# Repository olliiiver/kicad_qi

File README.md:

# Qi module designed in KiCad based on TI bq51013B

This is a "works for me" project. It has not been optimised (foreign object detection, max. output, etc) or tested for (unwanted) electromagnetic radiation.

## Photos

## BOM

- BQ51013BRHLR: http://www.ti.com/lit/ds/symlink/bq51013b.pdf
- 10 µH 0.15 Ω 3 A Coil (Würth  760308102210): https://www.we-online.de/katalog/datasheet/760308102210.pdf
https://www.conrad.de/de/p/wuerth-elektronik-we-wpcc-760308102210-empfaengerspule-qi-kompatibel-wireless-10-h-0-15-3-a-1-1364999.html
- All resistors and caps are 0805. Caps from coil to IC need to be min. 50V

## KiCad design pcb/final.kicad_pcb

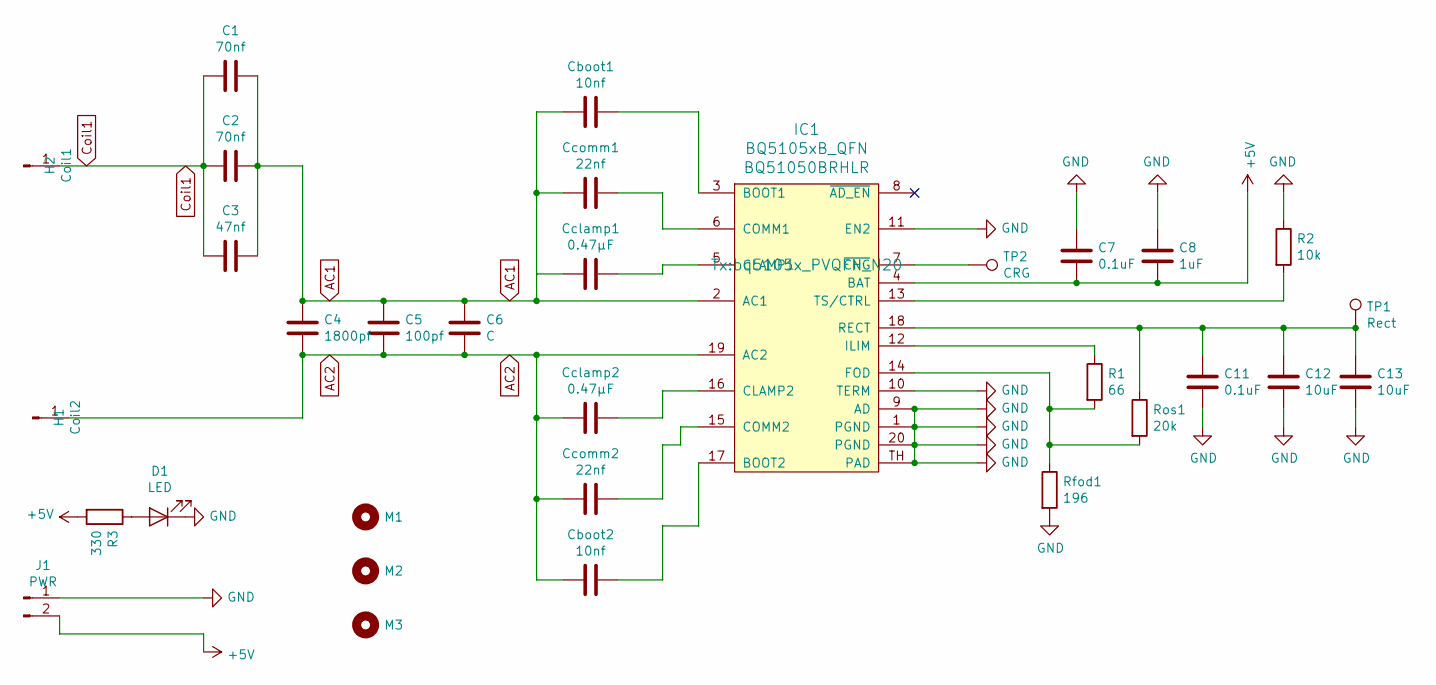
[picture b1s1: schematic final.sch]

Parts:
C1, C2: 70nf; C_0805_2012Metric_Pad1.15x1.40mm_HandSolder
C3: 47nf; C_0805_2012Metric_Pad1.15x1.40mm_HandSolder
C4: 1800pf; C_0805_2012Metric_Pad1.15x1.40mm_HandSolder
C5: 100pf; C_0805_2012Metric_Pad1.15x1.40mm_HandSolder
C6: C; C_0805_2012Metric_Pad1.15x1.40mm_HandSolder
C7, C11: 0.1uF; C_0805_2012Metric_Pad1.15x1.40mm_HandSolder
C8: 1uF; C_0805_2012Metric_Pad1.15x1.40mm_HandSolder
C12, C13: 10uF; C_0805_2012Metric_Pad1.15x1.40mm_HandSolder
Cboot1, Cboot2: 10nf; C_0805_2012Metric_Pad1.15x1.40mm_HandSolder
Cclamp1, Cclamp2: 0.47μF; C_0805_2012Metric_Pad1.15x1.40mm_HandSolder
Ccomm1, Ccomm2: 22nf; C_0805_2012Metric_Pad1.15x1.40mm_HandSolder
Coil1: H2; TestPoint_Pad_3.0x3.0mm
Coil2: H1; TestPoint_Pad_3.0x3.0mm
D1: LED; LED_0805_2012Metric_Pad1.15x1.40mm_HandSolder
IC1: BQ5105xB_QFN; bq5105x_PVQFN_N20; MPN BQ51050BRHLR
J1: PWR; PinHeader_1x02_P2.54mm_Vertical
M1, M2, M3: MountingHole; MountingHole_1152
R1: 66; R_0805_2012Metric_Pad1.15x1.40mm_HandSolder
R2: 10k; R_0805_2012Metric_Pad1.15x1.40mm_HandSolder
R3: 330; R_0805_2012Metric_Pad1.15x1.40mm_HandSolder
Rfod1: 196; R_0805_2012Metric_Pad1.15x1.40mm_HandSolder
Ros1: 20k; R_0805_2012Metric_Pad1.15x1.40mm_HandSolder
TP1: Rect; TestPoint_THTPad_D1.0mm_Drill0.5mm
TP2: CRG; TestPoint_THTPad_D1.0mm_Drill0.5mm

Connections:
+5V: C7.2, C8.2, IC1.4 (BAT), J1.2, R3.2
AC1: C1.1, C2.1, C3.1, C4.1, C5.1, C6.1, Cboot1.2, Cclamp1.2, Ccomm1.2, IC1.2 (AC1)
AC2: C4.2, C5.2, C6.2, Cboot2.2, Cclamp2.2, Ccomm2.2, Coil2.1, IC1.19 (AC2)
Coil1: C1.2, C2.2, C3.2, Coil1.1
GND: C7.1, C8.1, C11.2, C12.2, C13.2, D1.1 (K), IC1.1 (PGND), IC1.9 (AD), IC1.10 (TERM), IC1.11 (EN2), IC1.20 (PGND), IC1.TH (PAD), J1.1, R2.1, Rfod1.2
unnamed: C11.1, C12.1, C13.1, IC1.18 (RECT), Ros1.1, TP1.1
unnamed: Cboot1.1, IC1.3 (BOOT1)
unnamed: Cboot2.1, IC1.17 (BOOT2)
unnamed: Cclamp1.1, IC1.5 (CLAMP1)
unnamed: Cclamp2.1, IC1.16 (CLAMP2)
unnamed: Ccomm1.1, IC1.6 (COMM1)
unnamed: Ccomm2.1, IC1.15 (COMM2)
unnamed: D1.2 (A), R3.1
unnamed: IC1.7 (~CHG), TP2.1
unnamed: IC1.12 (ILIM), R1.1
unnamed: IC1.13 (TS/CTRL), R2.2
unnamed: IC1.14 (FOD), R1.2, Rfod1.1, Ros1.2

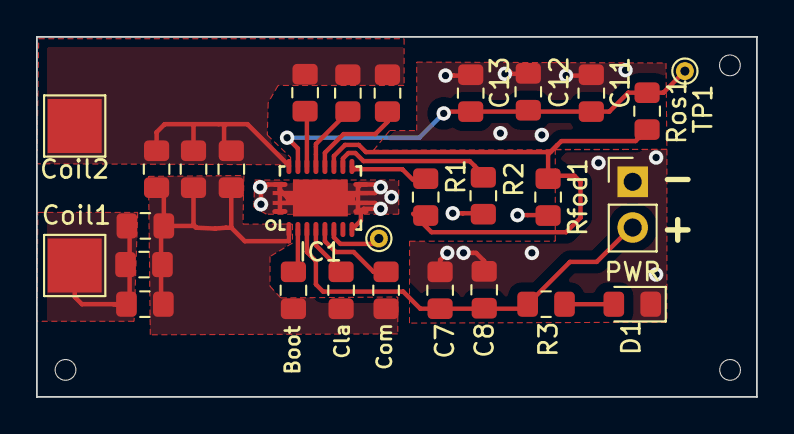
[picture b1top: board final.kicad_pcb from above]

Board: 2 copper layers, 40.0 x 20.0 mm, 32 parts (0 on the bottom side), 17 nets.

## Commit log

2020-05-13 first
